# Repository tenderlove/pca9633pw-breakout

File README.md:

# Breakout board for PCA9633PW

This is just a breakout board for the PCA9633.

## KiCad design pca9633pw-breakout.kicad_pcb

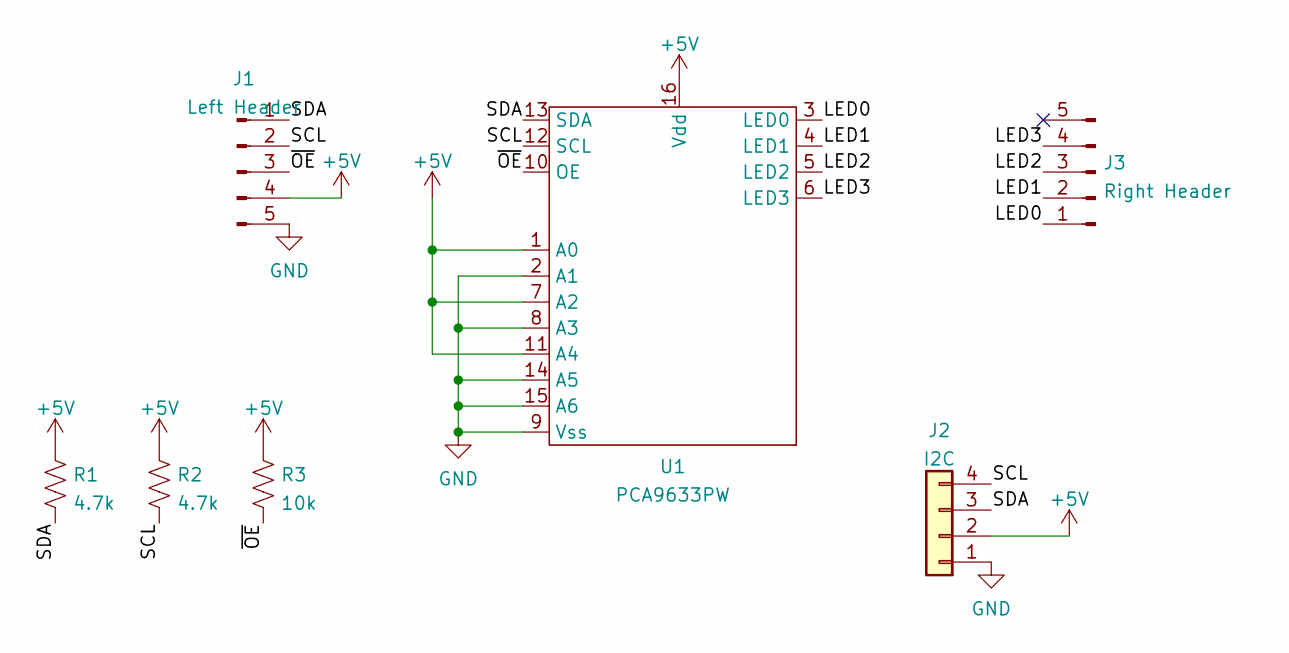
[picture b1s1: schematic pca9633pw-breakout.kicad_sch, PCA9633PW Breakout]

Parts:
J1: Left Header; PinHeader_1x05_P2.54mm_Vertical
J2: I2C; JST_SH_BM04B-SRSS-TB_1x04-1MP_P1.00mm_Vertical
J3: Right Header; PinHeader_1x05_P2.54mm_Vertical
R1, R2: 4.7k; R_1206_3216Metric_Pad1.30x1.75mm_HandSolder
R3: 10k; R_1206_3216Metric_Pad1.30x1.75mm_HandSolder
U1: PCA9633PW; TSSOP-16_4.4x5mm_P0.65mm

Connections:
+5V: J1.4, J2.2, R1.1, R2.1, R3.1, U1.1 (A0), U1.7 (A2), U1.11 (A4), U1.16 (Vdd)
/LED0: J3.1, U1.3 (LED0)
/LED1: J3.2, U1.4 (LED1)
/LED2: J3.3, U1.5 (LED2)
/LED3: J3.4, U1.6 (LED3)
/SCL: J1.2, J2.4, R2.2, U1.12 (SCL)
/SDA: J1.1, J2.3, R1.2, U1.13 (SDA)
/~OE: J1.3, R3.2, U1.10 (OE)
GND: J1.5, J2.1, U1.2 (A1), U1.8 (A3), U1.9 (Vss), U1.14 (A5), U1.15 (A6)

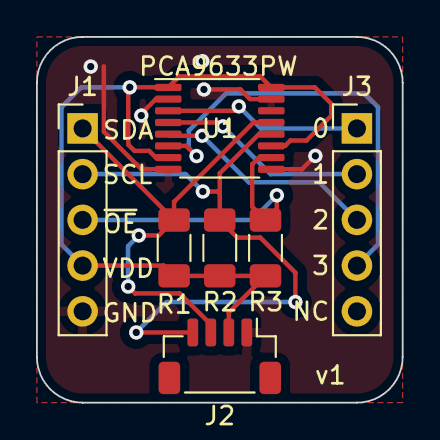
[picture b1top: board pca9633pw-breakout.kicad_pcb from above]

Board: 2 copper layers, 20.3 x 20.3 mm, 7 parts (0 on the bottom side), 9 nets.

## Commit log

2022-02-06 initial

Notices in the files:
pca9633pw-breakout.kicad_pcb:
CC BY 4.0
https://creativecommons.org/licenses/by/4.0
